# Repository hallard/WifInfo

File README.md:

WifInfo : Wifi Teleinfo server
==============================

This is a server board for Teleinfo French Meter Measure Library, it can be used as a stand alone device web server that can display/send Teleinfo information.

You can see Teleinformation official french datasheet [there][1]

Since this is really dedicated to French energy measuring system, I will continue in French

Pour le moment le logiciel utilisé doit être considéré comme une version béta (voir alpha), même si le hardware est parfaitement fonctionnel, la partie logicielle est loin d'être terminée.

##Fonctionnalités Terminées
- Mise à jour par Wifi (pas besoin de cable) 
- Affichage dans l'interface Web des données de Teleinfo 
- Affichage dans l'interface Web des données système 
- REST API du type http://wifinfo/papp pour récupérer l'étiquette PAPP (par exemple)

##Fonctionnalités à écrire
A terme les fonctionnalités de cette carte seront les suivantes :
- Créer la page WEB de connexion a un Wifi local 
- Créer la page WEB de configuration du Module 
- Envoi des données de téléinfo vers EMONCMS
- Envoi des données de téléinfo vers les box domotique (JEEDOM, EEDOMUS, ...)
- D'autres idées arriveront surement en cours de route...

Vous trouverez un article dédié à cette carte sur mon [blog][3]

##Schémas  

##Cartes 
&nbsp;
&nbsp;

##Documentation de la libraire LibTeleinfo
J'ai écrit un article [dédié][10] sur la librairie téléinfo qui est utilisée dans ce module. Vous pouvez aussi voir les [catégories][6] associées à la téléinfo sur mon [blog][7].

Pour les commentaires et le support vous pouvez allez sur le [forum][8] dédié ou dans la [communauté][9] 

##Sketch d'exemple
- [ESP8266_WebInfo][5] ESP8266 Web dynamic + Rest application. Attention version béta en cours de développement mais parfaitement fonctionnelle. 
- Article dédié à la carte [WifInfo][3]

##License
<br /><span xmlns:dct="http://purl.org/dc/terms/" property="dct:title">Wifinfo</span> by <a xmlns:cc="http://creativecommons.org/ns#" href="https://github.com/hallard/WifInfo" property="cc:attributionName" rel="cc:attributionURL">Charles-Henri Hallard</a> is licensed under a <a rel="license" href="http://creativecommons.org/licenses/by-nc-sa/4.0/">Creative Commons Attribution-NonCommercial-ShareAlike 4.0 International License</a>.<br />Based on a work at <a xmlns:dct="http://purl.org/dc/terms/" href="https://github.com/hallard/WifInfo" rel="dct:source">https://github.com/hallard/WifInfo</a>.

[1]: http://www.erdf.fr/sites/default/files/ERDF-NOI-CPT_02E.pdf
[2]: http://learn.adafruit.com/arduino-tips-tricks-and-techniques/arduino-libraries
[3]: https://hallard.me/wifiinfo/
[5]: https://github.com/hallard/LibTeleinfo/tree/master/examples/ESP8266_WifInfo
[6]: https://hallard.me/category/tinfo/
[7]: https://hallard.me
[8]: https://community.hallard.me/category/7
[9]: https://community.hallard.me
[10]: https://hallard.me/libteleinfo

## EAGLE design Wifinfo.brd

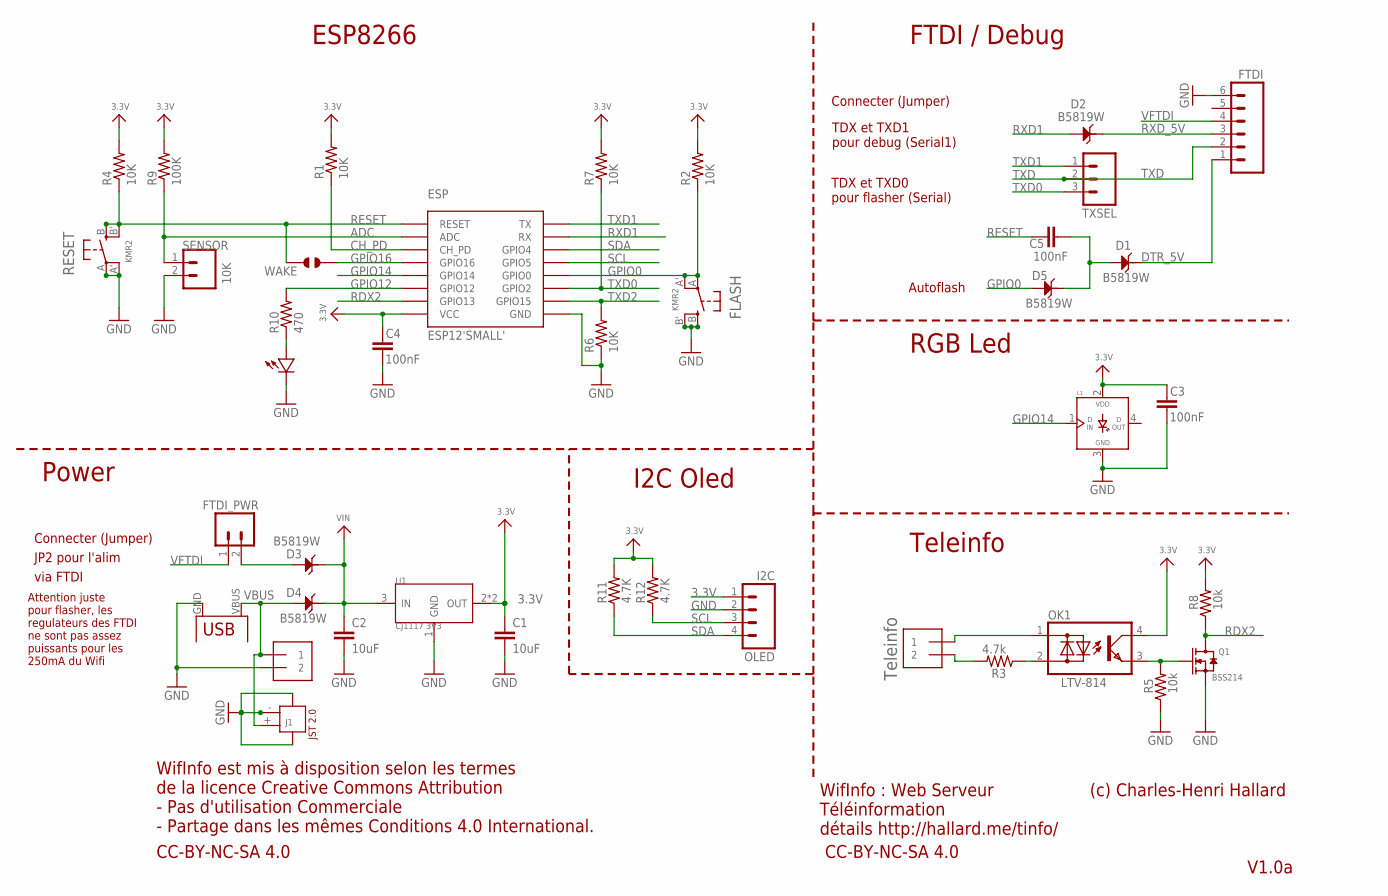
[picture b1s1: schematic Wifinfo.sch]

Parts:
C1, C2: 10uF; 0805-CAP
C3, C4, C5: 100nF; 0603-CAP
D1, D2, D3, D4, D5: B5819W; SOD123-2.7X1.6
ESP: ESP12'SMALL'; ESP08
FLASH: KMR2; BTN_KMR2_4.6X2.8
FTDI: M06SIP_LOCK_NO_SILK; 1X06-SIP_LOCK_NOSILK
FTDI_PWR: M02LOCK; 1X02_LOCK
J1: JST-2P-SMD'2.0'; 2P-SMD-2.0-90D
L1: WS2812B; WS2812-PTH
LED: RED; 0603-LED
OK1: LTV-814; DIL4-SMD
OLED: I2C; 1X04_LOCK
PWR: 1X2-3.5MM
Q1: BSS214; SOT23
R1, R2, R4, R6, R7: 10K; 0603-RES
R3: 4.7k; 0603-RES
R5, R8: 10k; 0603-RES
R9: 100K; 0805-RES
R10: 470; 0603-RES
R11, R12: 4.7K; 0603-RES
RESET: KMR2; BTN_KMR2_4.6X2.8
SENSOR: 10K; 1X02
TINFO: 1X2-3.5MM
TXSEL: M03LOCK; 1X03_LOCK
U1: CJ1117 3V3; SOT89
USB: USB; USB_MINIB_POWER
WAKE: JUMPER_SOLDER_1X2

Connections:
3.3V: C1.1, C3.2, C4.2, ESP.VCC, L1.2 (VDD), OK1.4 (C), OLED.1, R1.2, R2.2, R4.2, R7.2, R8.2, R9.2, R11.2, R12.2, U1.2 (OUT), U1.4 (OUT)
ADC: ESP.ADC, R9.1, SENSOR.1
CH_PD: ESP.CH_PD, R1.1
DTR_5V: D1.2, FTDI.1
GND: C1.2, C2.2, C3.1, C4.1, ESP.GND, FLASH.B (S), FLASH.B' (S1), FTDI.6, J1.3, J1.4, J1.- (2), L1.3 (GND), LED.MINUS, OLED.2, PWR.2, Q1.2 (S), R5.1, R6.1, RESET.A, RESET.A' (P1), SENSOR.2, U1.1 (GND), USB.GND
GPIO0: D5.1, ESP.GPIO0, FLASH.A, FLASH.A' (P1), R2.1
GPIO12: ESP.GPIO12, R10.2
GPIO14: ESP.GPIO14, L1.1 (DIN)
GPIO16: ESP.GPIO16, WAKE.2
unnamed: OK1.3 (E), Q1.1 (G), R5.2
unnamed: D3.1, FTDI_PWR.2
unnamed: OK1.2 (AC2), R3.1
unnamed: OK1.1 (AC1), TINFO.1
unnamed: R3.2, TINFO.2
unnamed: LED.PLUS, R10.1
unnamed: C5.1, D1.1, D5.2
RDX2: ESP.GPIO13, Q1.3 (D), R8.1
RESET: C5.2, ESP.RESET, R4.1, RESET.B (S), RESET.B' (S1), WAKE.1
RXD1: D2.1, ESP.RX
RXD_5V: D2.2, FTDI.3
SCL: ESP.GPIO5, OLED.3, R12.1
SDA: ESP.GPIO4, OLED.4, R11.1
TXD: FTDI.2, TXSEL.2
TXD0: ESP.GPIO2, R7.1, TXSEL.3
TXD1: ESP.TX, TXSEL.1
TXD2: ESP.GPIO15, R6.2
VBUS: D4.1, J1.+ (1), PWR.1, USB.VBUS (VCC)
VFTDI: FTDI.4, FTDI_PWR.1
VIN: C2.1, D3.2, D4.2, U1.3 (IN)

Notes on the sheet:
Teleinfo
WifInfo : Web Serveur Téléinformation détails http://hallard.me/tinfo/
CC-BY-NC-SA 4.0
WifInfo est mis à disposition selon les termes de la licence Creative Commons Attribution - Pas d'utilisation Commerciale - Partage dans les mêmes Conditions 4.0 International.
(c) Charles-Henri Hallard
Power
ESP8266
FTDI / Debug
RGB Led
I2C Oled
TDX et TXD0 pour flasher (Serial)
TDX et TXD1 pour debug (Serial1)
Connecter (Jumper)
JP2 pour l'alim
via FTDI
Attention juste pour flasher, les regulateurs des FTDI ne sont pas assez puissants pour les 250mA du Wifi
JST 2.0
Autoflash
V1.0a

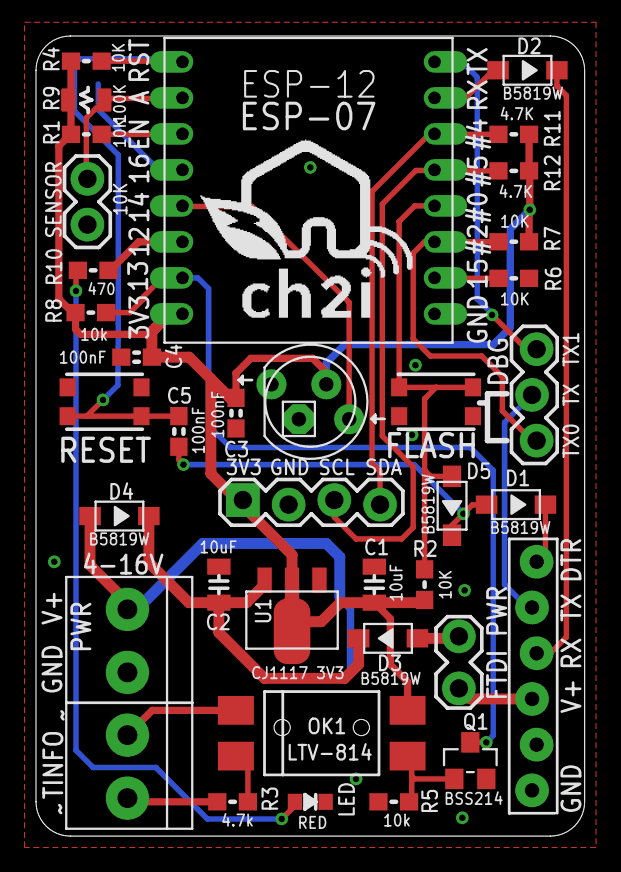
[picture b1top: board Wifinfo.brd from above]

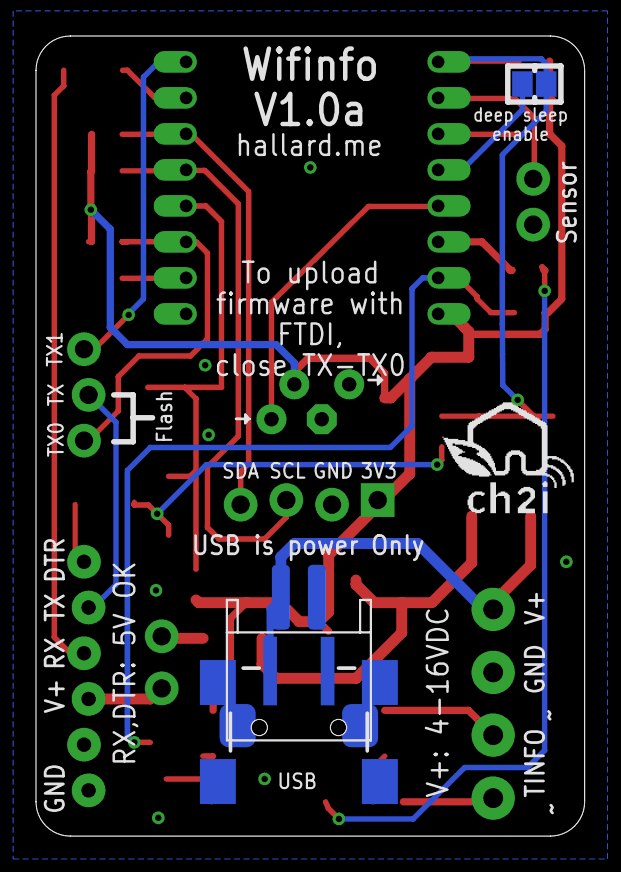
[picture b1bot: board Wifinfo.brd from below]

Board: 2 copper layers, 30.5 x 44.5 mm, 42 parts (4 on the bottom side), 29 nets.

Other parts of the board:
U$11: LOGO_CH2I_110MM
U$12: LOGO_CH2I_75MM

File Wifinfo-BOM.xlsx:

WifInfo BOM
Composants à positionner
Parts | Qty | Value | Device | Package | Sourcing | Description
R9 | 1 | 100K | RESISTOR0805-RES | 0805-RES |  | Resistor 100K 1%
C3, C4, C5 | 3 | 100nF | CAP0603-CAP | 0603-CAP |  | Capacitor
R1, R2, R4, R5, R6, R7, R8 | 7 | 10K | RESISTOR0603-RES | 0603-RES |  | Resistor
C1, C2 | 2 | 10uF | CAP0805-CAP | 0805-CAP |  | Capacitor
R3, R11, R12 | 3 | 4.7K | RESISTOR0603-RES | 0603-RES |  | Resistor
R10 | 1 | 470 | RESISTOR0603-RES | 0603-RES |  | Resistor
D1, D2, D3, D4, D5 | 5 | B5819W | DIODE-SCHOTTKY | SOD123 |  | Diodes schottky 1A 20V
LED | 1 | RED | LED0603 | 0603-LED
Q1 | 1 | BSS214 | BSS214NH6327XT | SOT23 | mouser | MOSFET N, BSS214 BSS170 ou CJ2302
U1 | 1 | CJ1117 3V3 | AZ1117CR-3.3TRG1 | SOT89 | mouser | 1A Low Dropout 3V3 Linear Regulator
ESP | 1 | ESP8266 | ESP-12F |  | ElectroDragon | ESP8266 Wifi module 12
FLASH, RESET | 2 | KMR2 | PTS810 SJK 250 SMTR LFS | 4.6X2.8 | mouser | SMT Tactiles Switches
OK1 | 1 | LTV-814 | LTV-814S | DIL4-SMD | mouser | Optocoupler, Phototransistor Output, AC Input
USB | 1 | USB | USB_POWER | USB_MINIB_POWER |  | Connecteur USB
L1 | 1 | WS2812 | PL9823-F5 | PTH | AliExpress | RGB LED with integrated controller 5MM
Connectique
FTDI_PWR | 1 | FTDI PWR | M02LOCK | 1X02-2.54mm |  | Header 2 points Male 2.54mm
TXSEL | 1 |  | M03LOCK | 1X03-2.54mm |  | Header 3 points Male 2.54mm
FTDI | 1 | FTDI con | M06LOCK | 1X06-2.54mm |  | Header 6 points Male 2.54mm
OLED | 1 | I2C con | M04LOCK | 1X04-2.54mm |  | Header 4 points femelle 2.54mm
PWR, TINFO | 2 | 1X2-3.5MM | 1X2-3.5MM | 1X2 points 3.5MM |  | 3.5mm Terminal block 2x2pt ou 1x4pt

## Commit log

2015-07-25 :confetti_ball: Added .gitattributes & .gitignore files
2015-07-25 Creation
2015-07-25 Corrected links
2015-07-27 Ajout fonction auto-flash
    Ajout fonction auto flash, pour pouvoir flasher le module avec un
    adaptateur FTDI like mais sans devoir appuyer sur le bouton flash
2015-07-29 Erreur liens
2015-07-29 Ajout lien article blog
2015-12-01 Minor Adjustments
    Minor Adjustments

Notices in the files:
parts and their libraries:
microbuilder: This work is placed in the public domain, and may be freely used for commercial and non-commercial work with the following conditions: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
SparkFun-Connectors: Licensing: Creative Commons ShareAlike 4.0 International - https://creativecommons.org/licenses/by-sa/4.0
